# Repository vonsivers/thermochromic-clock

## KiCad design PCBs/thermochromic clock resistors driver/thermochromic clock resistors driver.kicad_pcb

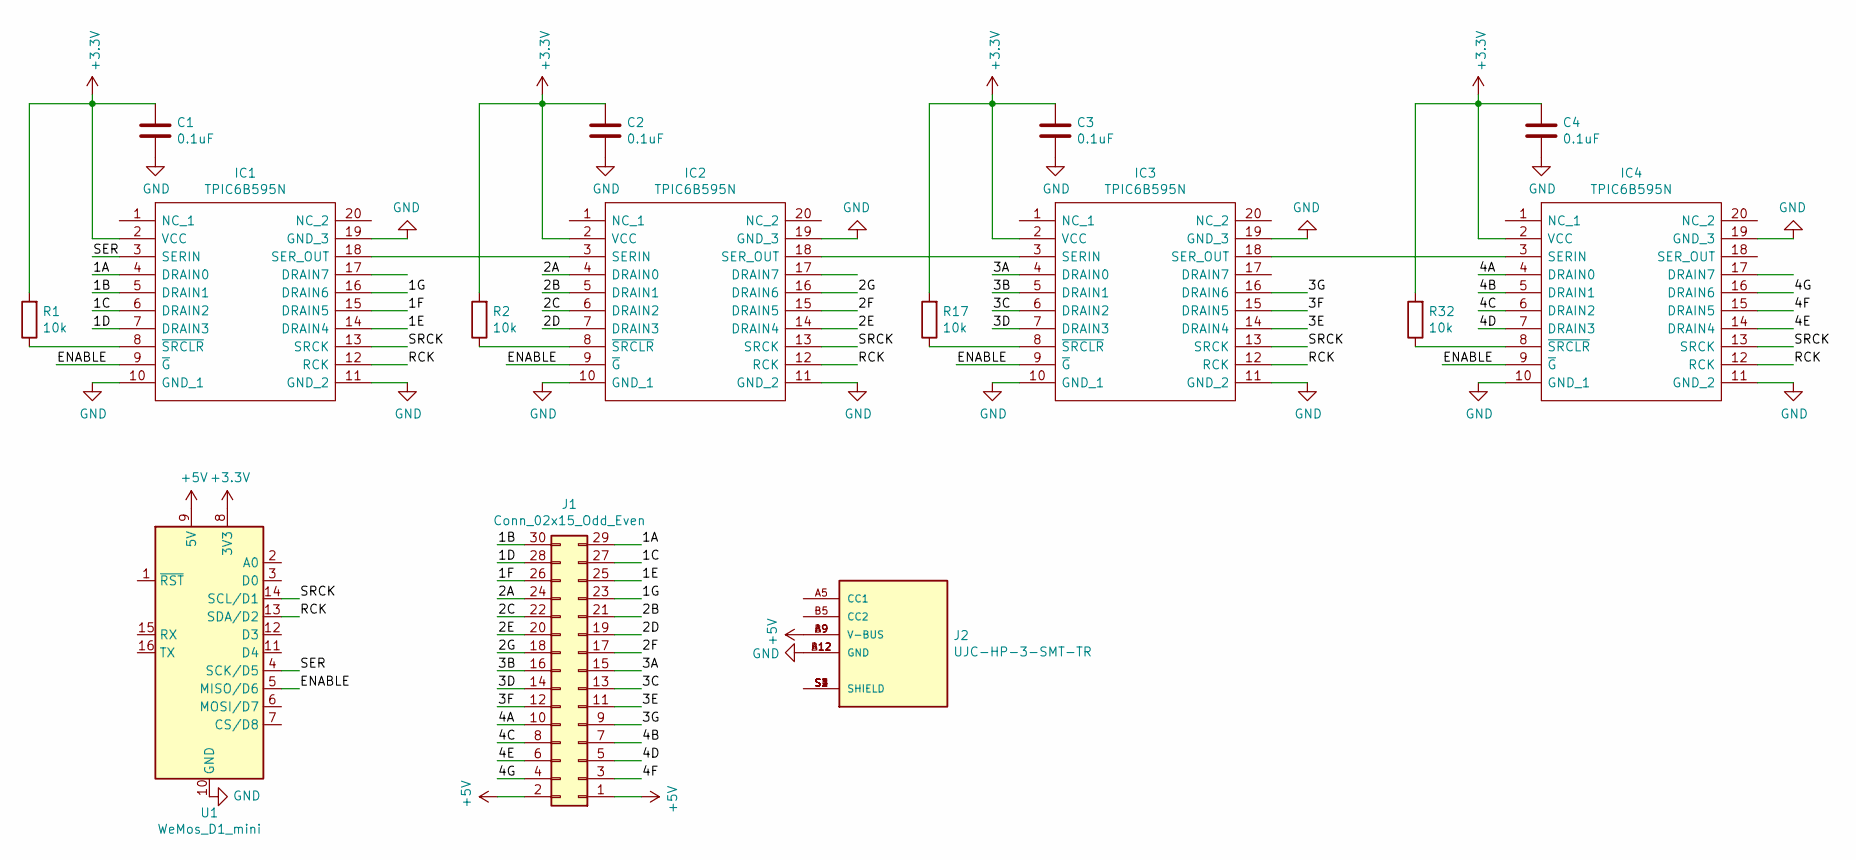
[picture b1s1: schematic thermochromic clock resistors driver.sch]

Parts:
C1, C2, C3, C4: 0.1uF; C_0805_2012Metric_Pad1.15x1.40mm_HandSolder
IC1, IC2, IC3, IC4: TPIC6B595N; DIP794W53P254L2540H508Q20N; Mouser Part Number 595-TPIC6B595N
J1: Conn_02x15_Odd_Even; PinSocket_2x15_P2.54mm_Vertical
J2: UJC-HP-3-SMT-TR; CUI_UJC-HP-3-SMT-TR; PARTREV 1.0
R1, R2, R17, R32: 10k; R_0805_2012Metric_Pad1.15x1.40mm_HandSolder
U1: WeMos_D1_mini; WEMOS_D1_mini_light

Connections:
+3V3: C1.1, C2.1, C3.1, C4.1, IC1.2 (VCC), IC2.2 (VCC), IC3.2 (VCC), IC4.2 (VCC), R1.2, R2.2, R17.2, R32.2, U1.8 (3V3)
+5V: J1.1, J1.2, J2.A9 (V-BUS), J2.B9 (V-BUS), U1.9 (5V)
/1A: IC1.4 (DRAIN0), J1.29
/1B: IC1.5 (DRAIN1), J1.30
/1C: IC1.6 (DRAIN2), J1.27
/1D: IC1.7 (DRAIN3), J1.28
/1E: IC1.14 (DRAIN4), J1.25
/1F: IC1.15 (DRAIN5), J1.26
/1G: IC1.16 (DRAIN6), J1.23
/2A: IC2.4 (DRAIN0), J1.24
/2B: IC2.5 (DRAIN1), J1.21
/2C: IC2.6 (DRAIN2), J1.22
/2D: IC2.7 (DRAIN3), J1.19
/2E: IC2.14 (DRAIN4), J1.20
/2F: IC2.15 (DRAIN5), J1.17
/2G: IC2.16 (DRAIN6), J1.18
/3A: IC3.4 (DRAIN0), J1.15
/3B: IC3.5 (DRAIN1), J1.16
/3C: IC3.6 (DRAIN2), J1.13
/3D: IC3.7 (DRAIN3), J1.14
/3E: IC3.14 (DRAIN4), J1.11
/3F: IC3.15 (DRAIN5), J1.12
/3G: IC3.16 (DRAIN6), J1.9
/4A: IC4.4 (DRAIN0), J1.10
/4B: IC4.5 (DRAIN1), J1.7
/4C: IC4.6 (DRAIN2), J1.8
/4D: IC4.7 (DRAIN3), J1.5
/4E: IC4.14 (DRAIN4), J1.6
/4F: IC4.15 (DRAIN5), J1.3
/4G: IC4.16 (DRAIN6), J1.4
/ENABLE: IC1.9 (~G), IC2.9 (~G), IC3.9 (~G), IC4.9 (~G), U1.5 (MISO/D6)
/RCK: IC1.12 (RCK), IC2.12 (RCK), IC3.12 (RCK), IC4.12 (RCK), U1.13 (SDA/D2)
/SER: IC1.3 (SERIN), U1.4 (SCK/D5)
/SRCK: IC1.13 (SRCK), IC2.13 (SRCK), IC3.13 (SRCK), IC4.13 (SRCK), U1.14 (SCL/D1)
GND: C1.2, C2.2, C3.2, C4.2, IC1.10 (GND_1), IC1.11 (GND_2), IC1.19 (GND_3), IC2.10 (GND_1), IC2.11 (GND_2), IC2.19 (GND_3), IC3.10 (GND_1), IC3.11 (GND_2), IC3.19 (GND_3), IC4.10 (GND_1), IC4.11 (GND_2), IC4.19 (GND_3), J2.A12 (GND), J2.B12 (GND), U1.10 (GND)
unnamed: IC1.8 (~SRCLR), R1.1
unnamed: IC1.18 (SER_OUT), IC2.3 (SERIN)
unnamed: IC2.8 (~SRCLR), R2.1
unnamed: IC2.18 (SER_OUT), IC3.3 (SERIN)
unnamed: IC3.8 (~SRCLR), R17.1
unnamed: IC3.18 (SER_OUT), IC4.3 (SERIN)
unnamed: IC4.8 (~SRCLR), R32.1
unnamed: J2.S1 (SHIELD), J2.S2 (SHIELD), J2.S3 (SHIELD), J2.S4 (SHIELD)

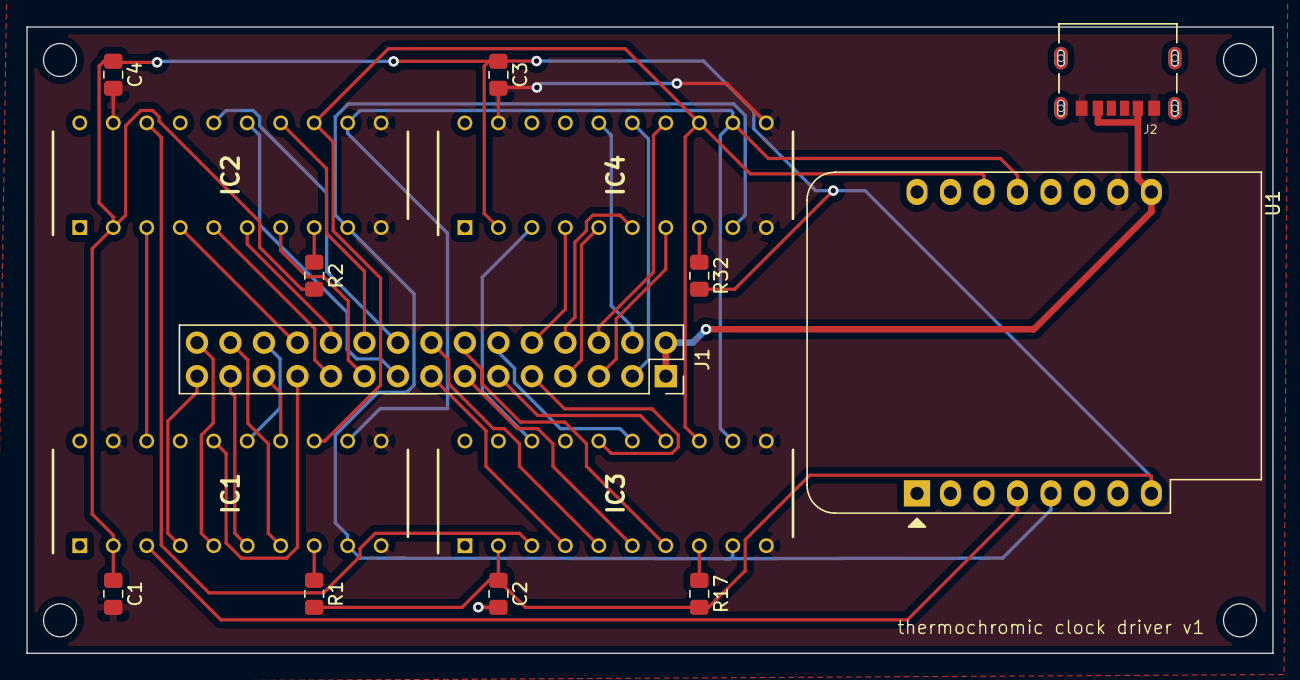
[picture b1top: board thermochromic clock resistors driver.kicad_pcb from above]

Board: 2 copper layers, 94.5 x 47.5 mm, 15 parts (0 on the bottom side), 43 nets.

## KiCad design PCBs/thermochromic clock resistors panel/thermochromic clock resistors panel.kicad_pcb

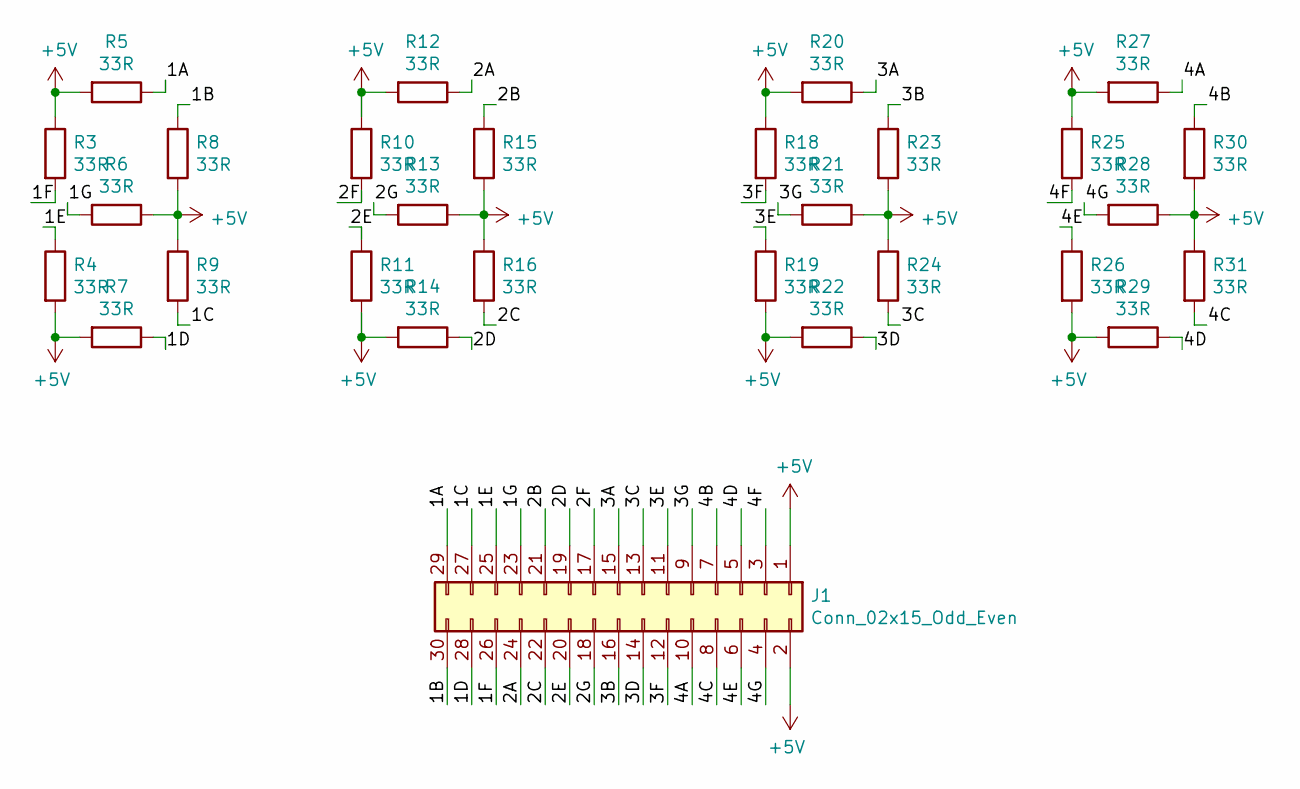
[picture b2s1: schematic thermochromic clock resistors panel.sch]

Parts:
J1: Conn_02x15_Odd_Even; PinHeader_2x15_P2.54mm_Horizontal
R3, R4, R5, R6, R7, R8, R9, R10, R11, R12, R13, R14, R15, R16, R18, R19, R20, R21, R22, R23, R24, R25, R26, R27, R28, R29, R30, R31: 33R; R_2512_6332Metric

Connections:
+5V: J1.1, J1.2, R3.1, R4.2, R5.2, R6.1, R7.2, R8.2, R9.1, R10.1, R11.2, R12.2, R13.1, R14.2, R15.2, R16.1, R18.1, R19.2, R20.2, R21.1, R22.2, R23.2, R24.1, R25.1, R26.2, R27.2, R28.1, R29.2, R30.2, R31.1
/1A: J1.29, R5.1
/1B: J1.30, R8.1
/1C: J1.27, R9.2
/1D: J1.28, R7.1
/1E: J1.25, R4.1
/1F: J1.26, R3.2
/1G: J1.23, R6.2
/2A: J1.24, R12.1
/2B: J1.21, R15.1
/2C: J1.22, R16.2
/2D: J1.19, R14.1
/2E: J1.20, R11.1
/2F: J1.17, R10.2
/2G: J1.18, R13.2
/3A: J1.15, R20.1
/3B: J1.16, R23.1
/3C: J1.13, R24.2
/3D: J1.14, R22.1
/3E: J1.11, R19.1
/3F: J1.12, R18.2
/3G: J1.9, R21.2
/4A: J1.10, R27.1
/4B: J1.7, R30.1
/4C: J1.8, R31.2
/4D: J1.5, R29.1
/4E: J1.6, R26.1
/4F: J1.3, R25.2
/4G: J1.4, R28.2

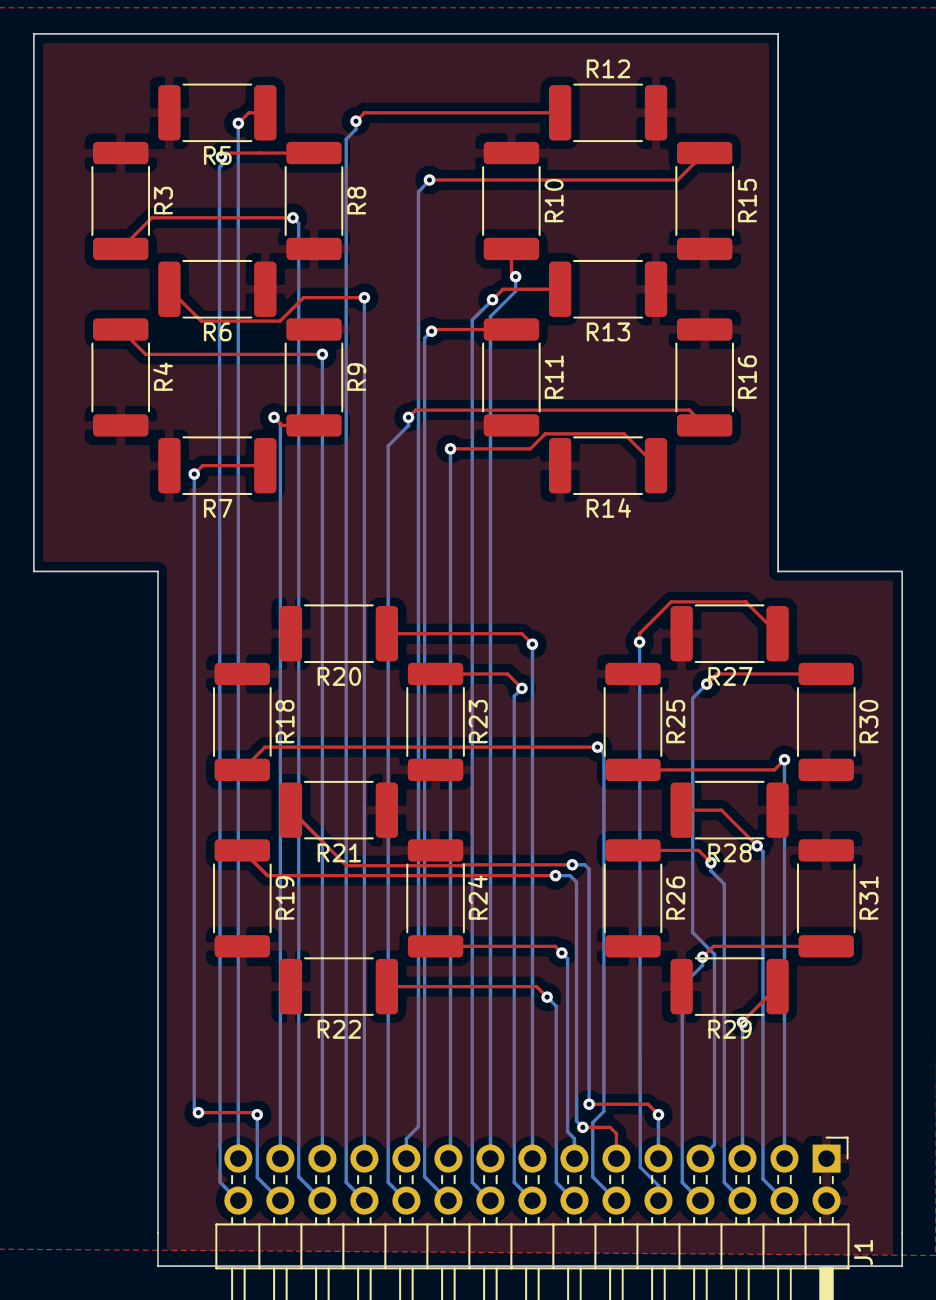
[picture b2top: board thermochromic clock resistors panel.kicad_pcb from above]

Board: 4 copper layers, 52.5 x 74.5 mm, 29 parts (0 on the bottom side), 29 nets.

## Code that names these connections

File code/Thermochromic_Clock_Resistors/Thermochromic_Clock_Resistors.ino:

#include <Wire.h>
#include <ESP8266WiFi.h>            // we need wifi to get internet access
#include <time.h>                   // time() ctime()

#include <WiFiManager.h> // https://github.com/tzapu/WiFiManager

//#define DEBUG // activate output to serial

#ifdef DEBUG
#define DEBUG_PRINT(x) Serial.print(x)
#define DEBUG_PRINTF(x, f) Serial.print(x, f)
#define DEBUG_PRINTLN(x) Serial.println(x)
#define DEBUG_PRINTLNF(x, f) Serial.println(x, f)
#else
#define DEBUG_PRINT(x)
#define DEBUG_PRINTF(x, f)
#define DEBUG_PRINTLN(x)
#define DEBUG_PRINTLNF(x, f)
#endif

//Pin connected to latch pin (RCK)
#define latchPin D2
//Pin connected to clock pin (SRCK)
#define clockPin D1
////Pin connected to Data in (SER IN)
#define dataPin D5
////Pin connected to enable (G_bar)
#define enablePin D6

/* Configuration of NTP */
#define MY_NTP_SERVER "de.pool.ntp.org"            // set the best fitting NTP server (pool) for your location
#define MY_TZ "CET-1CEST,M3.5.0,M10.5.0/3"        // https://github.com/nayarsystems/posix_tz_db/blob/master/zones.csv

time_t now;                         // this is the epoch
tm tm;                              // the structure tm holds time information in a more convient way
 
uint8_t lastMinute;                 // save minute when clock was last updated

bool PWMmode = true;               // PWM heating on/off

// PWM mode
//// PWM period (ms)
const uint16_t period = 50;
//// duty cycle
const double duty = 0.4;
//// heating duration (ms)
const uint16_t t_heatPWM = 10000;

// continous mode
//// heating time (ms)
const uint16_t t_heat = 1500;

// bits to activate for showing numbers 0...9
const byte seg[10] = {0b00111111, 0b00000110, 0b01011011, 0b01001111, 0b01100110, 0b01101101, 0b01111101, 0b00000111, 0b01111111, 0b01101111};
   

void setup() {
  //set pins to output because they are addressed in the main loop
  pinMode(latchPin, OUTPUT);
  pinMode(dataPin, OUTPUT);  
  pinMode(clockPin, OUTPUT);
  pinMode(enablePin, OUTPUT);

  digitalWrite(enablePin, LOW);
  
  Serial.begin(115200);

  // delay a little
  delay(1000);
  
  WiFi.mode(WIFI_STA); // explicitly set mode, esp defaults to STA+AP
  
  //WiFiManager
  //Local intialization. Once its business is done, there is no need to keep it around
  WiFiManager wm;
  //reset settings - for testing
  //wm.resetSettings();

  //fetches ssid and pass and tries to connect
  //if it does not connect it starts an access point with the specified name
  //and goes into a blocking loop awaiting configuration
  if (!wm.autoConnect("ThermochromicAP")) {
    DEBUG_PRINTLN("failed to connect Wifi and hit timeout");
    //reset and try again, or maybe put it to deep sleep
    ESP.restart();
    delay(1000);
  }
  DEBUG_PRINTLN("Wifi connected");

  configTime(MY_TZ, MY_NTP_SERVER); // configure NTP server and timezone

  delay(2000);
  
  showTime();
  if(PWMmode) {
    updateDisplayPWM();
  }
  else {
    updateDisplay();
  }
  lastMinute = tm.tm_min;

}

void loop() {
  //testDisplayPWM();
  showTime();
  if(tm.tm_min!=lastMinute) {
    DEBUG_PRINTLN("updating display");
    if(PWMmode) {
      DEBUG_PRINTLN("PWM heating on");
      updateDisplayPWM();
      DEBUG_PRINTLN("PWM heating off");
    }
    else {
      DEBUG_PRINTLN("heating on");
      updateDisplay();
      DEBUG_PRINTLN("heating off");
    }
    lastMinute = tm.tm_min;
  }
  delay(1000);
  
}

void showTime() {
  time(&now);                       // read the current time
  localtime_r(&now, &tm);           // update the structure tm with the current time
  DEBUG_PRINT("year:");
  DEBUG_PRINT(tm.tm_year + 1900);  // years since 1900
  DEBUG_PRINT("\tmonth:");
  DEBUG_PRINT(tm.tm_mon + 1);      // January = 0 (!)
  DEBUG_PRINT("\tday:");
  DEBUG_PRINT(tm.tm_mday);         // day of month
  DEBUG_PRINT("\thour:");
  DEBUG_PRINT(tm.tm_hour);         // hours since midnight  0-23
  DEBUG_PRINT("\tmin:");
  DEBUG_PRINT(tm.tm_min);          // minutes after the hour  0-59
  DEBUG_PRINT("\tsec:");
  DEBUG_PRINT(tm.tm_sec);          // seconds after the minute  0-61*
  DEBUG_PRINT("\twday");
  DEBUG_PRINT(tm.tm_wday);         // days since Sunday 0-6
  if (tm.tm_isdst == 1)             // Daylight Saving Time flag
    DEBUG_PRINT("\tDST");
  else
    DEBUG_PRINT("\tstandard");
  DEBUG_PRINTLN();
}

void updateDisplay() {

  uint16_t dig1 = tm.tm_hour / 10;
  uint16_t dig2 = tm.tm_hour % 10;
  uint16_t dig3 = tm.tm_min / 10;
  uint16_t dig4 = tm.tm_min % 10;

  // turn outputs on
  writeByte(seg[dig4]);
  writeByte(seg[dig3]);
  writeByte(seg[dig2]);
  writeByte(seg[dig1]);
  delay(t_heat);
  
  // turn all outputs off
  for (int i=0; i<4; ++i) {
    writeByte(0);
  }

}

void updateDisplayPWM() {

  uint16_t dig1 = tm.tm_hour / 10;
  uint16_t dig2 = tm.tm_hour % 10;
  uint16_t dig3 = tm.tm_min / 10;
  uint16_t dig4 = tm.tm_min % 10;

  // heat segments for some time
  for(int t=0; t<t_heatPWM; t+=period) {
    // turn outputs on
    writeByte(seg[dig4]);
    writeByte(seg[dig3]);
    writeByte(seg[dig2]);
    writeByte(seg[dig1]);
    delay(duty*period);
    
    // turn all outputs off
    for (int i=0; i<4; ++i) {
      writeByte(0);
    }
    delay((1-duty)*period);
  }

}


void testDisplayPWM() {
  // loop over numbers 0..9
  for(int i=0; i<10; ++i) {
    // show number for 60 seconds
    for(int t=0; t<60000; t+=period) {
      // loop over digits 1..4
      for(int j=0; j<4; ++j) {
        writeByte(seg[i]);  // show same number for all digits
      }
      delay(duty*period);
      // turn all segments off
      for(int j=0; j<4; ++j) {
        writeByte(0); 
      }
      delay((1-duty)*period);
    }
  } 
}



void testDisplay() {
  // loop over numbers 0..9
  for(int i=0; i<10; ++i) {
    // loop over digits 1..4
    for(int j=0; j<4; ++j) {
      writeByte(seg[i]);  // show same number for all digits
    }
    delay(t_heat);
    // turn all segments off
    for(int j=0; j<4; ++j) {
      writeByte(0); 
    }
    delay(60000-t_heat);
  }
  
}



// This method sends bits to the shift register:
//
void writeByte(byte bitsToSend) {

  // turn off the output so the pins don't light up
  // while you're shifting bits:
  digitalWrite(latchPin, LOW);
  
  // shift the bits out
  shiftOut(dataPin, clockPin, MSBFIRST, bitsToSend);

  // turn on the output so the LEDs can light up:
  digitalWrite(latchPin, HIGH);

}

void registerWrite(int whichPin, int whichState) {
  // the bits you want to send
  byte bitsToSend0 = 0;
  // write number as bits
  bitWrite(bitsToSend0, whichPin, whichState);

  // turn off the output so the pins don't light up
  // while you're shifting bits:
  digitalWrite(latchPin, LOW);
  
  // shift the bits out
  shiftOut(dataPin, clockPin, MSBFIRST, bitsToSend0);

  // turn on the output so the LEDs can light up:
  digitalWrite(latchPin, HIGH);
}

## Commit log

2021-06-12 PCB BoM added
2022-03-11 added wifi manager
